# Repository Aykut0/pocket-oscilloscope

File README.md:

# Pocket Oscilloscope

A pocket-sized, battery-powered oscilloscope board built around an ESP32-S3. PCB design project.

The probe input goes through a protected front end (a Schottky clamp to the rails) into op-amp buffer and scaling stages, with a switch for the input range so both small and larger signals fit the ADC. An ESP32-S3-MINI-1 module digitizes the signal, and its USB and wireless links can carry the waveform to a computer or phone. A single-cell LiPo with an on-board USB-C charger and a 3.3 V regulator lets it run untethered. Reset and boot buttons, status LEDs and test points are there for bring-up.

## Files

```
hardware/                 KiCad project (open pocket_oscilloscope.kicad_pro)
hardware/fabrication/     Gerber files
docs/images/              render and schematic
```

Open the project in KiCad 8 or newer. Some parts use the KiCad PCM "AKL" libraries; install them from the Plugin and Content Manager if symbols show as missing.

The board design and fabrication files are complete. Firmware is not part of this repository yet.

---

Yaşar Aykut Altuntop · Koç University · [LinkedIn](https://linkedin.com/in/aykutaltuntop) · [GitHub](https://github.com/Aykut0)

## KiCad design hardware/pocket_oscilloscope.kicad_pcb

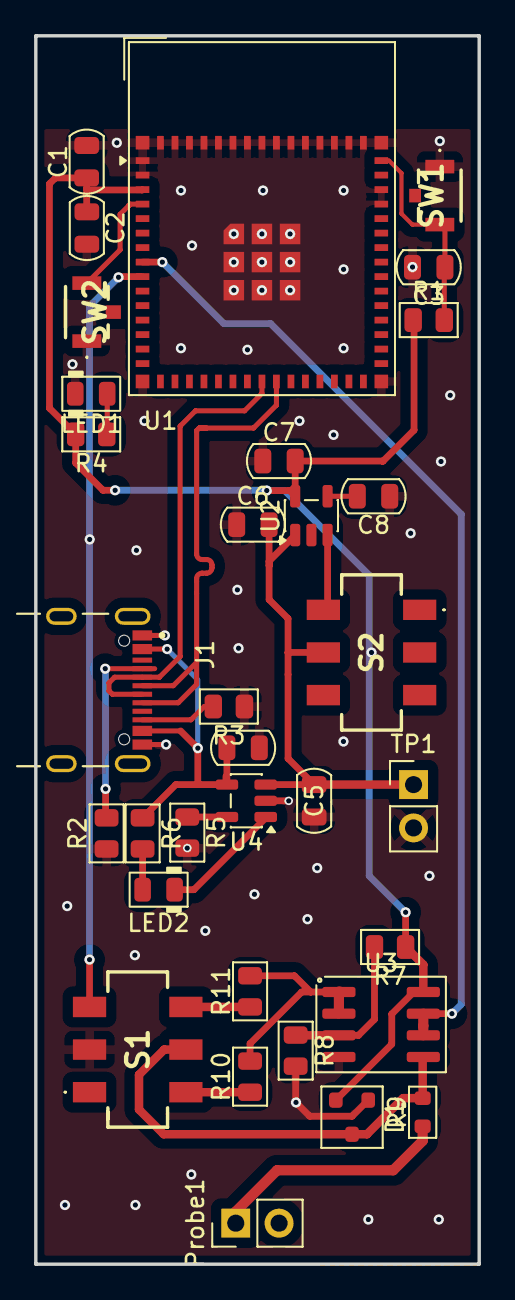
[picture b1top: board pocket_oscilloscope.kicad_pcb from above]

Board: 2 copper layers, 26.0 x 72.0 mm, 33 parts (0 on the bottom side), 23 nets.

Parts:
C1: 22uF; C_0805_2012Metric
C2: 0.1uF; C_0805_2012Metric
C3, C6: 1uF; C_0805_2012Metric
C4, C5, C7: 2.2uF; C_0805_2012Metric
C8: 18nF; C_0805_2012Metric
D1: BAT54S; SOT-23
J1: UJ20-C-H-G-SMT-4-P16-TR; SAMESKY_UJ20-C-H-G-SMT-4-P16-TR
LED1, LED2: LED_0805_2012Metric
Probe1: Pomona 5133; PinHeader_1x02_P2.54mm_Vertical
R1, R4, R7, R8: 10k; R_0805_2012Metric
R2, R3: 5.1k; R_0805_2012Metric
R5: 2k; R_0805_2012Metric
R6: 1k; R_0805_2012Metric
R9: 1M; R_0603_1608Metric
R10: 1.2M; R_0805_2012Metric
R11: 56k; R_0805_2012Metric
S1, S2: SLW-913535-2A-SMT; SLW9135352ASMT
SW1: RST; TL1017AABF160QG
SW2: BOOT; TL1017AABF160QG
TP1: Battery V_In; PinHeader_1x02_P2.54mm_Vertical
U1: ESP32-S3-MINI-1; ESP32-S2-MINI-1
U2: SPX3819M5-L-3-3; SOT-23-5
U3: MCP6022; SOIC-8_3.9x4.9mm_P1.27mm
U4: MCP73831; SOT-23-5

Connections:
+3.3V: C1.1, C2.1, C7.2, D1.2 (K), R1.1, R4.2, R7.1, U1.3 (3V3), U2.5 (OUT), U3.8 (V+)
+3.7V: C5.2, C6.2, S2.5 (COM_2), TP1.1, U2.1 (IN), U4.3 (V_{BAT})
+5V: C4.1, J1.A4_B9 (VBUS), J1.B4_A9 (VBUS__1), R6.1, U4.4 (V_{DD})
/ADC_Input: U1.8 (IO4), U3.6 (-), U3.7
/D+: J1.A6 (DP1), J1.B6 (DP2), U1.24 (USB_D+)
/D-: J1.A7 (DN1), J1.B7 (DN2), U1.23 (USB_D-)
/RANGE_SENSE: S1.3 (NC_2), U1.9 (IO5)
/Raw_Signal: D1.3 (C), R9.2, S1.5 (COM_2), U3.5 (+)
/VG: R10.2, R11.2, U3.1, U3.2 (-)
GND: C1.2, C2.2, C3.2, C4.2, C5.1, C6.1, C7.1, C8.1, D1.1 (A), J1.A1_B12 (GND), J1.B1_A12 (GND__1), LED1.1 (K), R2.1, R3.1, R5.2, R8.2, S1.2 (COM_1), SW1.1 (A), SW2.1 (A), TP1.2, U1.1 (GND), U1.2 (GND), U1.42 (GND), U1.43 (GND), U1.46 (GND), U1.47 (GND), U1.48 (GND), U1.49 (GND), U1.50 (GND), U1.51 (GND), U1.52 (GND), U1.53 (GND), U1.54 (GND), U1.55 (GND), U1.56 (GND), U1.57 (GND), U1.58 (GND), U1.59 (GND), U1.60 (GND), U1.61 (GND), U1.62 (GND), U1.63 (GND), U1.64 (GND), U1.65 (GND), U2.2 (GND), U3.4 (V-), U4.2 (V_{SS})
unnamed: J1.A5 (CC1), R2.2
unnamed: J1.B5 (CC2), R3.2
unnamed: LED1.2 (A), R4.1
unnamed: LED2.2 (A), R6.2
unnamed: LED2.1 (K), U4.1 (STAT)
unnamed: Probe1.1, R9.1
unnamed: R10.1, S1.4 (NC_3)
unnamed: S2.4 (NC_3), U2.3 (EN)
unnamed: C3.1, R1.2, SW1.2 (B), U1.45 (EN)
unnamed: SW2.2 (B), U1.4 (IO0)
unnamed: C8.2, U2.4 (BP)
unnamed: R7.2, R8.1, U3.3 (+)
unnamed: R5.1, U4.5 (PROG)
